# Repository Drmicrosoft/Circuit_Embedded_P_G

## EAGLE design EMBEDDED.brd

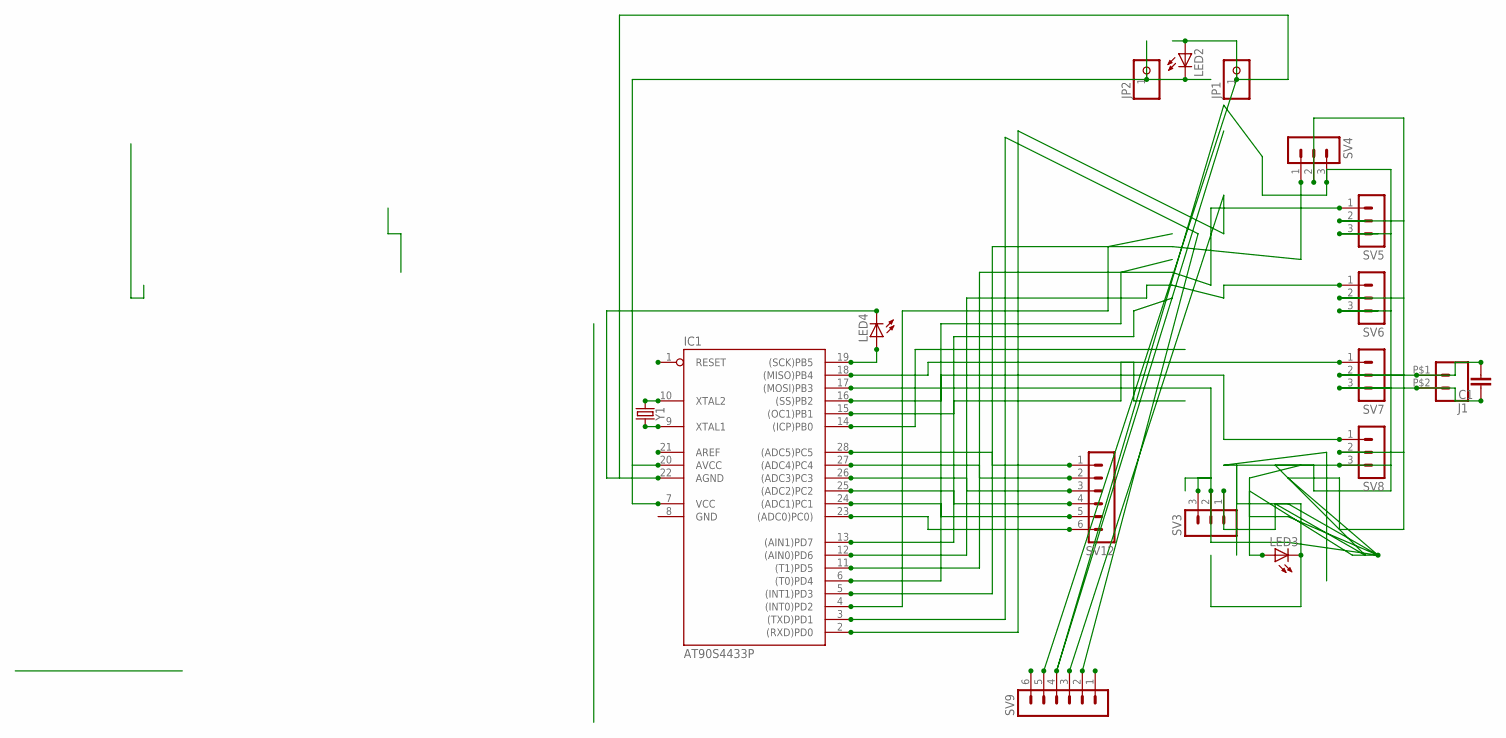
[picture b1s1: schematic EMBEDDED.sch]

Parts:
C1: C5/2.5; C5B2.5
IC1: AT90S4433P; DIL28-3
J1: CONN_02PTH2; 1X02_BIG
JP1, JP2: PINHD-1X1; 1X01
LED2, LED3, LED4: LEDLD260; LD260
SV3, SV4, SV5, SV6, SV7, SV8: MA03-1
SV9, SV12: MA06-1
Y1: CRYSTALPTH-HC49US; HC49US

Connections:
GND: IC1.8 (GND)
unnamed: IC1.17 ((MOSI)PB3), SV3.3
unnamed: C1.2, J1.P$1 (1), LED3.A, SV3.2, SV4.2, SV5.2, SV6.2, SV7.2, SV8.2
unnamed: IC1.22 (AGND), JP1.1, LED2.A, LED4.K (C), SV9.5
unnamed: IC1.7 (VCC), IC1.20 (AVCC), JP2.1, LED2.K (C)
unnamed: IC1.16 ((SS)PB2), SV8.1
unnamed: IC1.15 ((OC1)PB1), SV7.1
unnamed: IC1.12 ((AIN0)PD6), SV6.1
unnamed: IC1.28 ((ADC5)PC5), SV12.1
unnamed: IC1.11 ((T1)PD5), SV5.1
unnamed: IC1.9 (XTAL1), Y1.2
unnamed: IC1.5 ((INT1)PD3), SV4.1
unnamed: IC1.27 ((ADC4)PC4), SV12.2
unnamed: IC1.26 ((ADC3)PC3), SV12.3
unnamed: IC1.2 ((RXD)PD0), SV9.3
unnamed: IC1.3 ((TXD)PD1), SV9.2
unnamed: IC1.25 ((ADC2)PC2), SV12.4
unnamed: IC1.24 ((ADC1)PC1), SV12.5
unnamed: IC1.23 ((ADC0)PC0)), SV12.6
unnamed: IC1.10 (XTAL2), Y1.1
unnamed: IC1.19 ((SCK)PB5), LED4.A
OMAR: C1.1, J1.P$2 (2), LED3.K (C), SV3.1, SV4.3, SV5.3, SV6.3, SV7.3, SV8.3, SV9.4

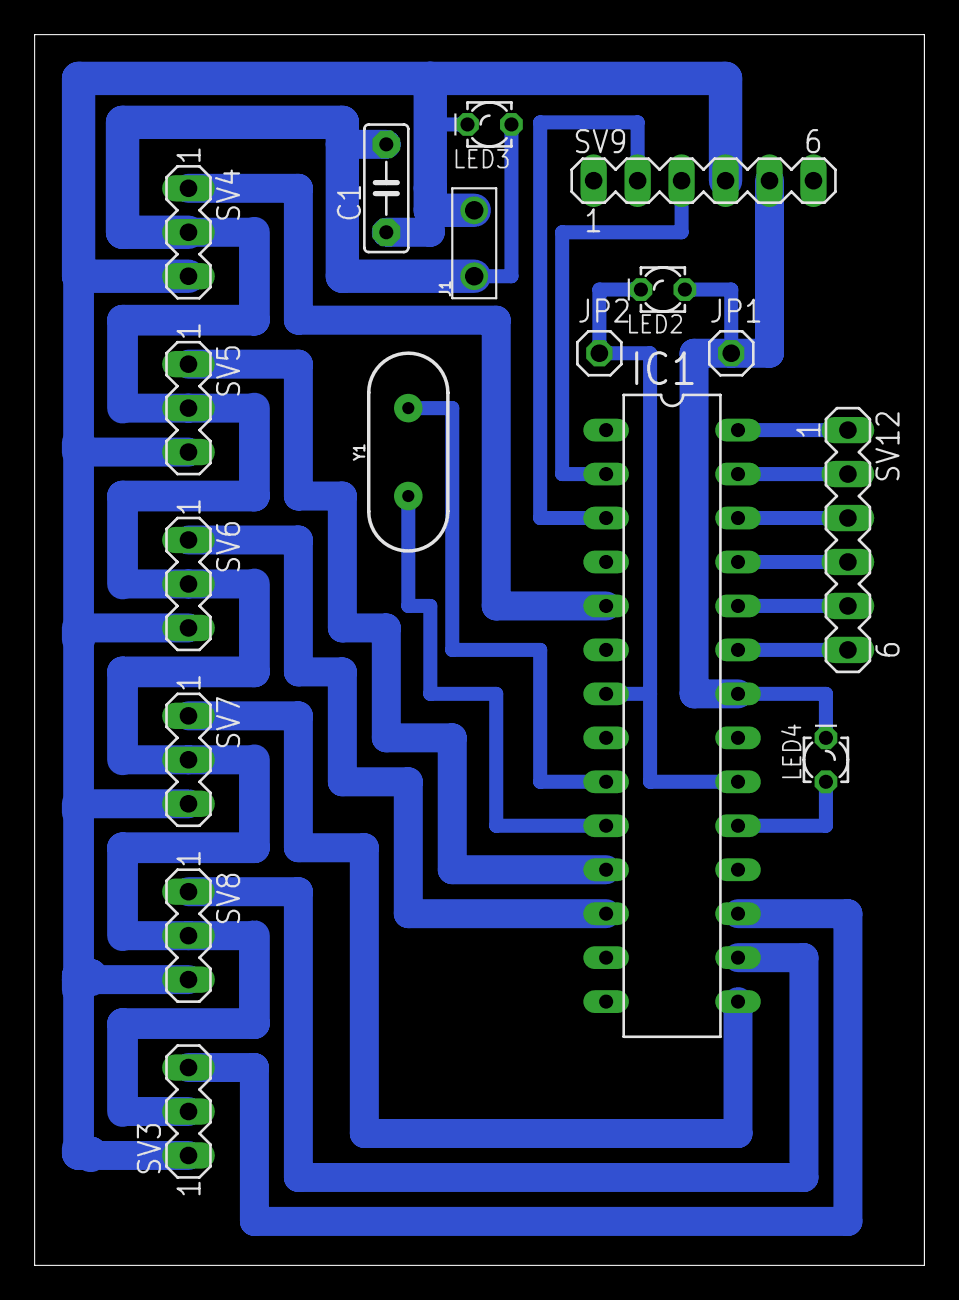
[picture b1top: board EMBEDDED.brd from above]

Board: 2 copper layers, 51.4 x 71.1 mm, 17 parts (0 on the bottom side), 21 nets.

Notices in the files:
parts and their libraries:
SparkFun-Connectors: Licensing: Creative Commons ShareAlike 4.0 International - https://creativecommons.org/licenses/by-sa/4.0
